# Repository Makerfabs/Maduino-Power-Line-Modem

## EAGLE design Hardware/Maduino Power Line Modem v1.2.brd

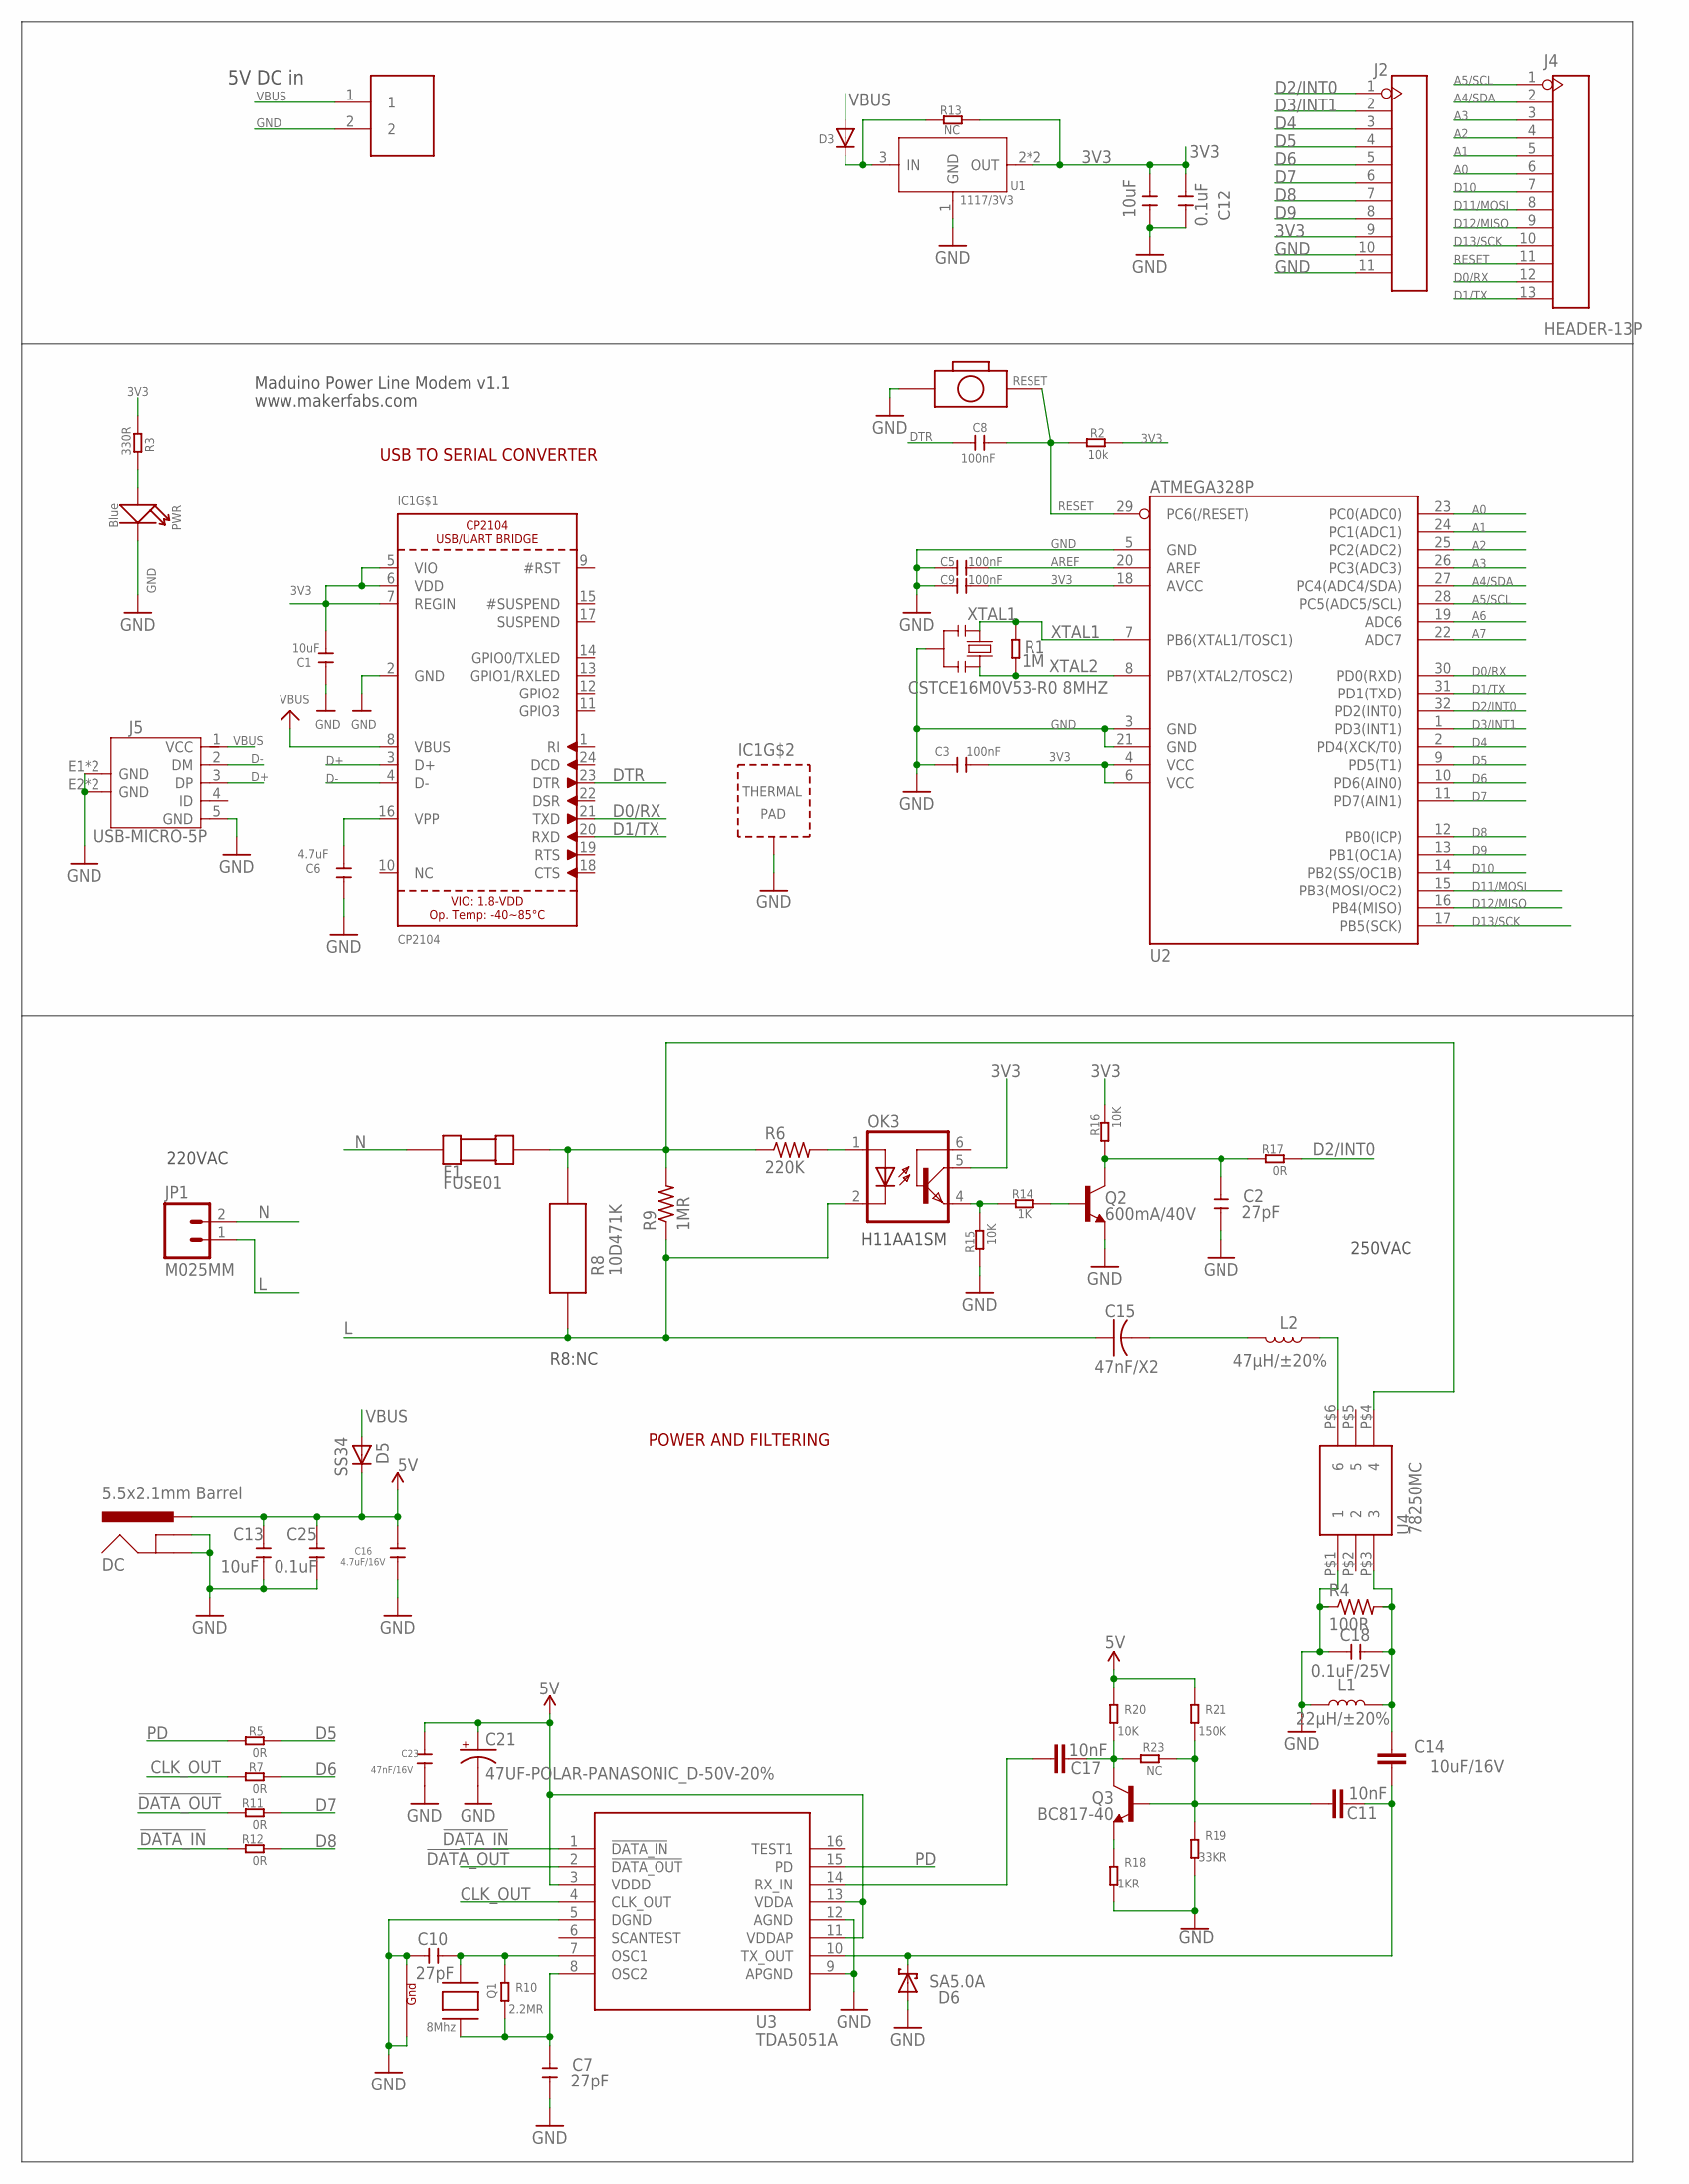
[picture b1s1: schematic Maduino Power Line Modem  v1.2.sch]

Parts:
C1, C4, C13: 10uF; 0603
C2, C7, C10: 27pF; 0603
C3, C5, C8, C9: 100nF; 0603
C6: 4.7uF; 0603
C11, C17: 10nF; 0603
C12, C25: 0.1uF; 0603
C14: 10uF/16V; 0603
C15: 47nF/X2; C150-054X183
C16: 4.7uF/16V; 0603
C18: 0.1uF/25V; 0603
C21: 47UF-POLAR-PANASONIC_D-50V-20%; PANASONIC_D
C23: 47nF/16V; 0603
D3: DIODESOD-323F; SOD-323F
D5: SS34; DO-214AC
D6: SA5.0A; DO41-10
DC: 5.5x2.1mm Barrel; POWER_JACK_SMD
F1: FUSE01
IC1: CP2104; QFN24_4MM_SMSC
J1: PH2.0-2P-90-DIP
J2: HEADER-11P-2.54; 11P-2.54
J4: HEADER-13P; 13P-2.54
J5: USB-MICRO-5P; MICRO-USB-5P
JP1: M025MM; SCREWTERMINAL-5MM-2
L1: 22µH/±20%; CR75
L2: 47µH/±20%; CR75
OK3: H11A1SM; DIL6-SMD
PWR: Blue; LED-0603
Q1: 8Mhz; NX3225
Q2: 600mA/40V; SOT23-3
Q3: BC817-40; SOT23-3
R1: 1M; R0603
R2: 10k; R0603
R3: 330R; R0603
R4: 100R; R1206
R5, R7, R11, R12, R17: 0R; R0603
R6: 220K; R1206
R8: 10D471K; DIP2-7.5MM
R9: 1MR; R1206
R10: 2.2MR; R0603
R13, R23: NC; R0603
R14: 1K; R0603
R15, R16, R20: 10K; R0603
R18: 1KR; R0603
R19: 33KR; R0603
R21: 150K; R0603
RESET: BOTTON-2P-90D; 2P-7.62X3.56-90D
U1: 1117/3V3; SOT89
U2: ATMEGA328P; TQFP32
U3: TDA5051A; SOT-162
U4: 78250MC; SMD6-254-1270X900
Y1: CSTCE16M0V53-R0 8MHZ; RESONATOR

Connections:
3V3: C1.2, C3.2, C4.2, C9.2, C12.2, IC1.5 (VIO), IC1.6 (VDD), IC1.7 (REGIN), J2.9, OK3.5 (COL), R2.1, R3.1, R13.1, R16.1, U1.2 (OUT), U1.4 (OUT), U2.4 (VCC), U2.6 (VCC), U2.18 (AVCC)
5V: C13.2, C16.1, C21.+, C23.1, C25.2, D5.C, DC.VIN0 (PWR), R20.1, R21.1, U3.3 (VDDD), U3.11 (VDDAP), U3.13 (VDDA)
!DATA_IN: R12.2, U3.1 (!DATA_IN)
!DATA_OUT: R11.2, U3.2 (!DATA_OUT)
A0: J4.6, U2.23 (PC0(ADC0))
A1: J4.5, U2.24 (PC1(ADC1))
A2: J4.4, U2.25 (PC2(ADC2))
A3: J4.3, U2.26 (PC3(ADC3))
A4/SDA: J4.2, U2.27 (PC4(ADC4/SDA))
A5/SCL: J4.1, U2.28 (PC5(ADC5/SCL))
A6: U2.19 (ADC6)
A7: U2.22 (ADC7)
AREF: C5.2, U2.20 (AREF)
CLK_OUT: R7.2, U3.4 (CLK_OUT)
D0/RX: IC1.21 (TXD), J4.12, U2.30 (PD0(RXD))
D1/TX: IC1.20 (RXD), J4.13, U2.31 (PD1(TXD))
D2/INT0: J2.1, R17.1, U2.32 (PD2(INT0))
D3/INT1: J2.2, U2.1 (PD3(INT1))
D4: J2.3, U2.2 (PD4(XCK/T0))
D5: J2.4, R5.1, U2.9 (PD5(T1))
D6: J2.5, R7.1, U2.10 (PD6(AIN0))
D7: J2.6, R11.1, U2.11 (PD7(AIN1))
D8: J2.7, R12.1, U2.12 (PB0(ICP))
D9: J2.8, U2.13 (PB1(OC1A))
D10: J4.7, U2.14 (PB2(SS/OC1B))
D11/MOSI: J4.8, U2.15 (PB3(MOSI/OC2))
D12/MISO: J4.9, U2.16 (PB4(MISO))
D13/SCK: J4.10, U2.17 (PB5(SCK))
D+: IC1.3 (D+), J5.3 (DP)
D-: IC1.4 (D-), J5.2 (DM)
DTR: C8.1, IC1.23 (DTR)
GND: C1.1, C2.2, C3.1, C4.1, C5.1, C6.1, C7.2, C9.1, C10.1, C12.1, C13.1, C16.2, C18.1, C21.-, C23.2, C25.1, D6.A, DC.GND (GNDBREAK), DC.P$4 (GND), IC1.2 (GND), IC1.THERM (TP), J1.2, J2.10, J2.11, J5.5 (GND), J5.E1 (GND), J5.E2 (GND), J5.P1 (GND), J5.P2 (GND), L1.P$1 (1), PWR.-, Q1.2 (G2), Q1.4 (G1), Q2.2 (E), R4.1, R15.2, R18.2, R19.2, RESET.P$2 (2), U1.1 (GND), U2.3 (GND), U2.5 (GND), U2.21 (GND), U3.5 (DGND), U3.9 (APGND), U3.12 (AGND), U4.P$1 (1), Y1.2
L: C15.1, JP1.1, OK3.2 (C), R8.P$2 (2), R9.1
N: F1.P$1, JP1.2
unnamed: OK3.1 (A), R6.2
unnamed: C7.1, Q1.3 (X2), R10.2, U3.8 (OSC2)
unnamed: C17.2, U3.14 (RX_IN)
unnamed: L2.P$1 (1), U4.P$6 (6)
unnamed: OK3.4 (EMI), R14.2, R15.1
unnamed: C14.1, C18.2, L1.P$2 (2), R4.2, U4.P$3 (3)
unnamed: PWR.+, R3.2
unnamed: Q2.1 (B), R14.1
unnamed: C15.2, L2.P$2 (2)
unnamed: C6.2, IC1.16 (VPP)
unnamed: C11.1, C14.2, D6.C, U3.10 (TX_OUT)
unnamed: D3.C, R13.2, U1.3 (IN)
unnamed: C17.1, Q3.3 (C), R20.2, R23.1
unnamed: C10.2, Q1.1 (X1), R10.1, U3.7 (OSC1)
unnamed: C2.1, Q2.3 (C), R16.2, R17.2
unnamed: F1.P$2, R6.1, R8.P$1 (1), R9.2, U4.P$4 (4)
unnamed: C11.2, Q3.1 (B), R19.1, R21.2, R23.2
unnamed: Q3.2 (E), R18.1
PD: R5.2, U3.15 (PD)
RESET: C8.2, J4.11, R2.2, RESET.P$1 (1), U2.29 (PC6(/RESET))
VBUS: D3.A, D5.A, IC1.8 (VBUS), J1.1, J5.1 (VCC)
XTAL1: R1.2, U2.7 (PB6(XTAL1/TOSC1)), Y1.1
XTAL2: R1.1, U2.8 (PB7(XTAL2/TOSC2)), Y1.3

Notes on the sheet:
USB TO SERIAL CONVERTER
Maduino Power Line Modem v1.1
www.makerfabs.com
POWER AND FILTERING
220VAC
250VAC
5V DC in
H11AA1SM
R8:NC

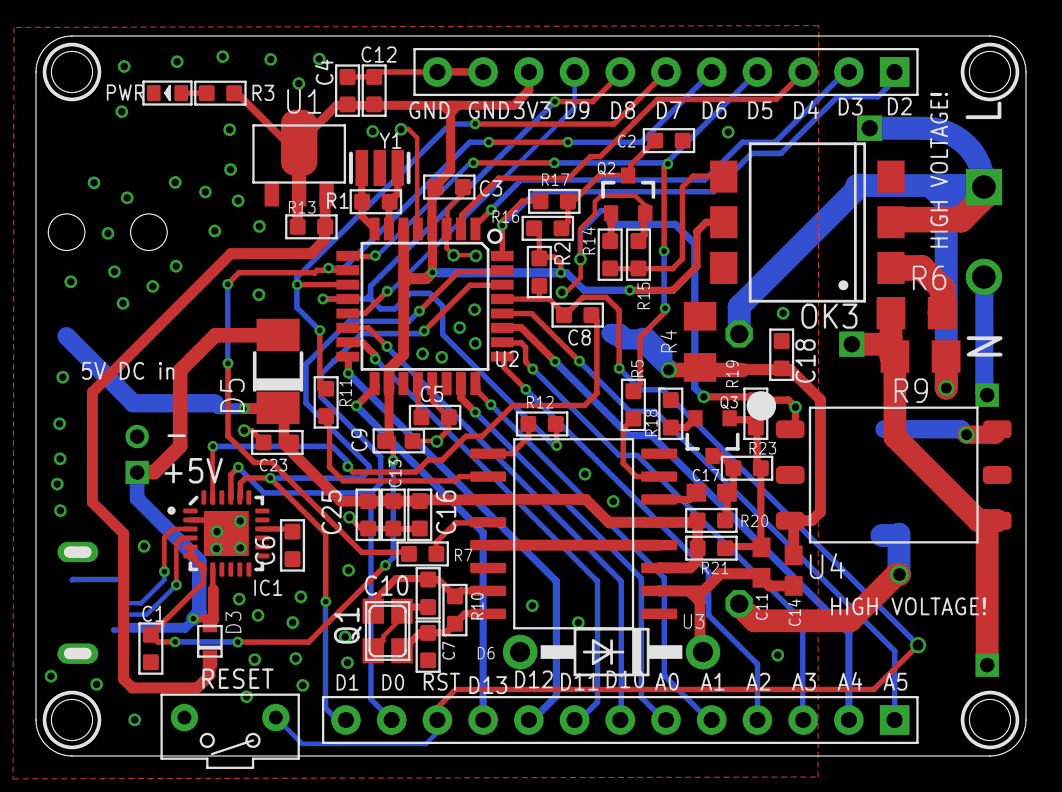
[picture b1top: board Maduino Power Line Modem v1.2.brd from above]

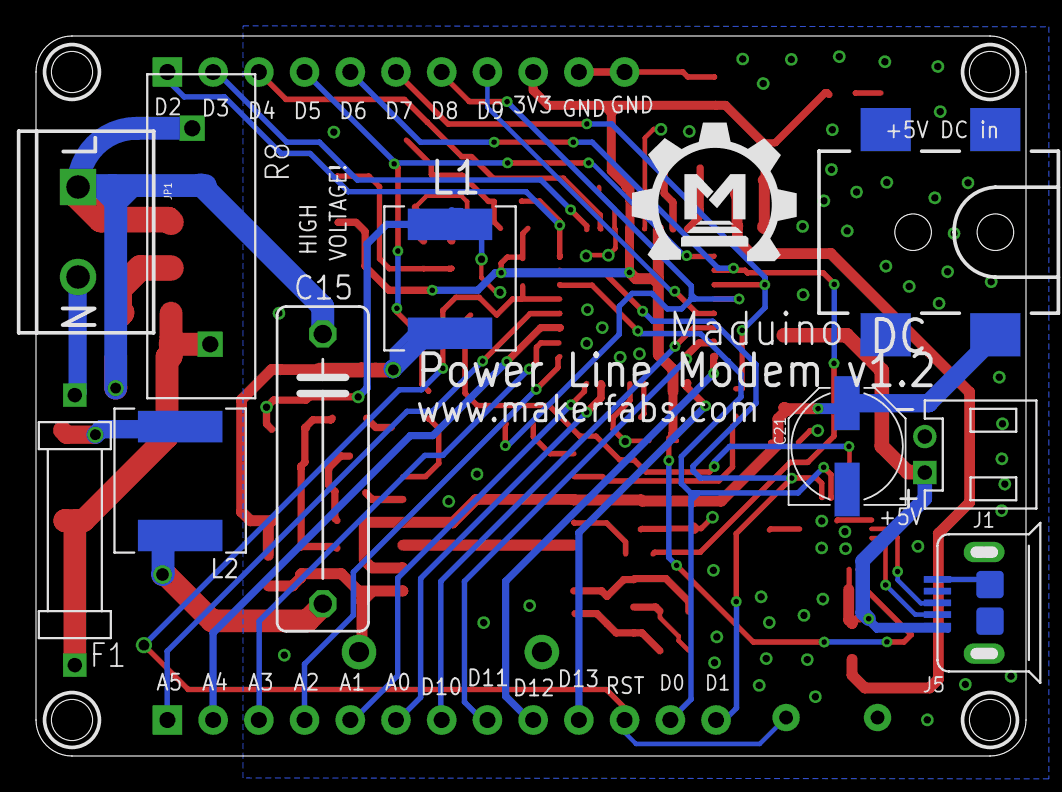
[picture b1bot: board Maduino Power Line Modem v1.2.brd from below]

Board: 2 copper layers, 54.4 x 39.4 mm, 68 parts (11 on the bottom side), 55 nets.

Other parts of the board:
U$1: MAKERFABS_0.3

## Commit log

2021-07-26 create hardware and demo

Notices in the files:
parts and their libraries:
microbuilder: This work is placed in the public domain, and may be freely used for commercial and non-commercial work with the following conditions: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
SparkFun-Capacitors: Licensing: Creative Commons ShareAlike 4.0 International - https://creativecommons.org/licenses/by-sa/4.0
